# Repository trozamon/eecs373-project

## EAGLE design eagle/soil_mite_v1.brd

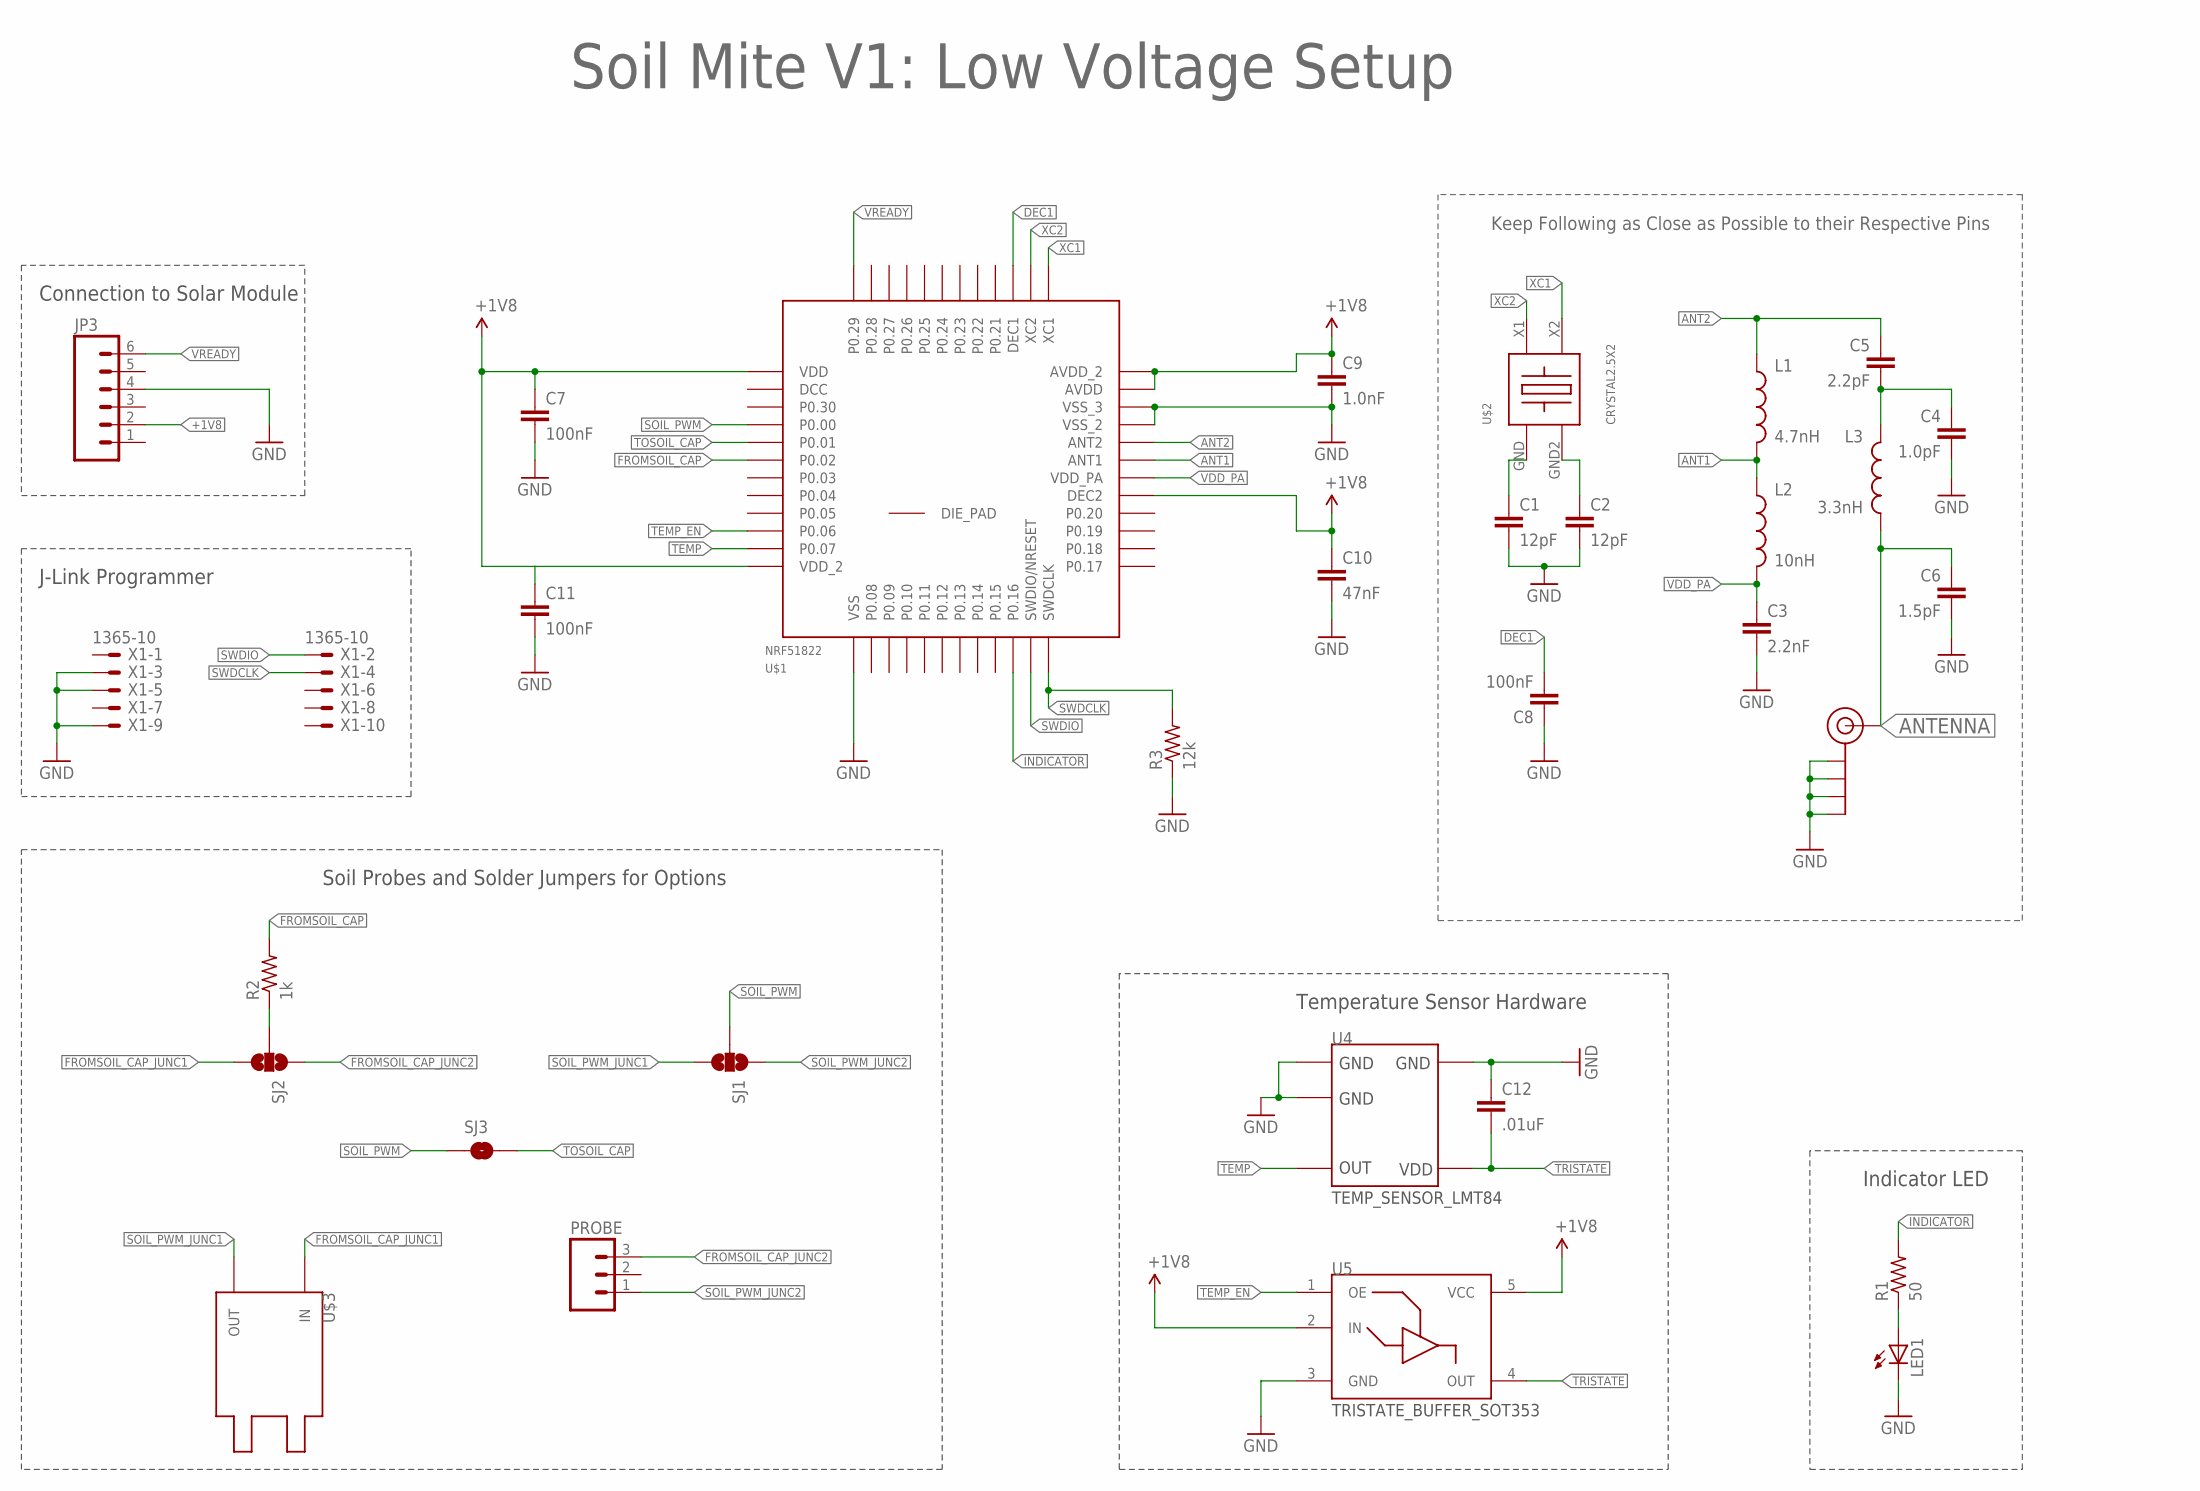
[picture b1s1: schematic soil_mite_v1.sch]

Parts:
C1, C2: 12pF; 0402-CAP
C3: 2.2nF; 0402-CAP
C4: 1.0pF; 0402-CAP
C5: 2.2pF; 0402-CAP
C6: 1.5pF; 0402-CAP
C7, C8, C11: 100nF; 0402-CAP
C9: 1.0nF; 0402-CAP
C10: 47nF; 0402-CAP
C12: .01uF; 0402-CAP
J$1: SMA_EDGE; SMA-EDGE
JP3: M06POLAR; MOLEX-1X6
L1: 4.7nH; C0402
L2: 10nH; C0402
L3: 3.3nH; C0402
LED1: JON_LIB_LEDCHIPLED_0603; JON_LIB_CHIPLED_0603
PROBE: M03PTH; 1X03
R1: 50; R0603
R2: 1k; R0603
R3: 12k; RCL_R0402
SJ1, SJ2: SOLDERJUMPER_2WAYT; SJ_2
SJ3: SOLDERJUMPERNO; SJ_2S-NO
U4: TEMP_SENSOR_LMT84; SOT353
U5: TRISTATE_BUFFER_SOT353; SOT353
U$1: NRF51822; QFN48
U$2: CRYSTAL2.5X2; 2.5X2MM
U$3: SOIL_PROBE_TOP_TOPOUT-IN; PROBE_LAYOUT_1_OUT-IN
X1: 1365-10

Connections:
+1V8: C7.1, C9.1, C10.1, C11.1, JP3.2, U5.2 (IN), U5.5 (VCC), U$1.1 (VDD), U$1.12 (VDD_2), U$1.29 (DEC2), U$1.35 (AVDD), U$1.36 (AVDD_2)
ANT1: L1.2, L2.1, U$1.31 (ANT1)
ANT2: C5.1, L1.1, U$1.32 (ANT2)
ANTENNA: C6.1, J$1.SIG (SIGNAL), L3.2
DEC1: C8.2, U$1.39 (DEC1)
FROMSOIL_CAP: R2.1, R2.2, SJ2.2, U$1.6 (P0.02)
FROMSOIL_CAP_JUNC1: SJ2.3, U$3.IN
FROMSOIL_CAP_JUNC2: PROBE.3, SJ2.1
GND: C1.2, C2.2, C3.2, C4.2, C6.2, C7.2, C8.1, C9.2, C10.2, C11.2, C12.1, J$1.GND@0 (GND), J$1.GND@1 (GND), J$1.GND@2 (GND), J$1.GND@3 (GND), JP3.4, LED1.C, R3.1, U4.1 (GND), U4.2 (GND), U4.5 (GND), U5.3 (GND), U$1.13 (VSS), U$1.33 (VSS_2), U$1.34 (VSS_3), X1.3, X1.5, X1.9
INDICATOR: R1.2, U$1.22 (P0.16)
unnamed: C1.1, U$2.GND
unnamed: C2.1, U$2.GND2
unnamed: LED1.A, R1.1
unnamed: C4.1, C5.2, L3.1
SOIL_PWM: SJ1.2, SJ3.1, U$1.4 (P0.00)
SOIL_PWM_JUNC1: SJ1.3, U$3.OUT
SOIL_PWM_JUNC2: PROBE.1, SJ1.1
SWDCLK: R3.2, U$1.24 (SWDCLK), X1.4
SWDIO: U$1.23 (SWDIO/NRESET), X1.2
TEMP: U4.3 (OUT), U$1.11 (P0.07)
TEMP_EN: U5.1 (OE), U$1.10 (P0.06)
TOSOIL_CAP: SJ3.2, U$1.5 (P0.01)
TRISTATE: C12.2, U4.4 (VDD), U5.4 (OUT)
VDD_PA: C3.1, L2.2, U$1.30 (VDD_PA)
VREADY: JP3.6, U$1.48 (P0.29)
XC1: U$1.37 (XC1), U$2.X2
XC2: U$1.38 (XC2), U$2.X1

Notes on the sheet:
Soil Mite V1: Low Voltage Setup
Keep Following as Close as Possible to their Respective Pins
Connection to Solar Module
J-Link Programmer
Soil Probes and Solder Jumpers for Options
Temperature Sensor Hardware
Indicator LED

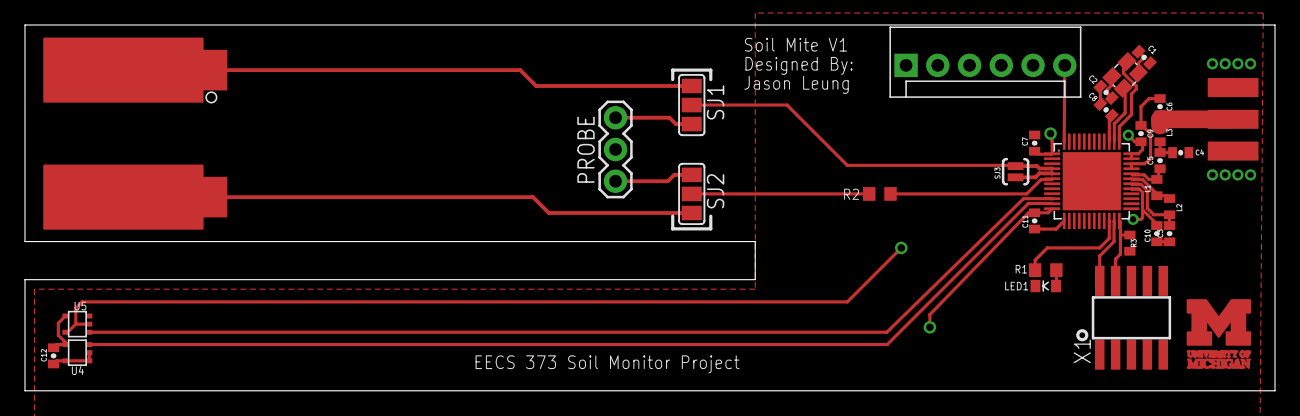
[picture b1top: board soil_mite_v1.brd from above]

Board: 4 copper layers, 100.0 x 29.3 mm, 32 parts (0 on the bottom side), 27 nets.

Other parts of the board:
U$5: BLOCK-M-DOUBLE-STACKED-5MM_MASK

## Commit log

2014-11-02 Add proposal, Makefiles
2014-11-02 Updat Makefile, add pics
2014-11-03 Update diagrams, proposal
2014-11-10 Start system document, it's pretty jank right now.
2014-11-12 Update system document
2014-11-13 Update system documentation
2014-11-16 Add power circuit schematic
2014-11-21 Update power schematic
2014-11-21 Add temp sensor to system docs
2014-11-21 added completed schematic but incomplete board. if you need explanations of parts of the board feel free to ping me
2014-11-21 Finish schematic, assigning footprints
2014-11-21 Finish power component to footprint mapping
2014-11-22 Finalize schematic
2014-11-22 Add initial power board design
2014-11-23 updated files. need to understand new components
2014-11-23 need to route board. 'layout' part done. need eagle professional to finish
2014-11-23 finished layout. let me know if there are glaring errors
2014-11-23 Minor updates to power schematic and board
2014-11-23 Add pull-downs to NMOS gates on power board
2014-11-23 Update gitignore
2014-11-23 finalized soil mite design. sending out for shipping
2014-11-23 Add gerber stuffz
2014-12-03 Redo power schematic
2014-12-03 Finish power schematic bugfixes
2014-12-03 Attach footprints to components
2014-12-03 Small fixes to schematic, netlist
2014-12-03 Layout PCB
2014-12-03 Finish PCB layout
2014-12-03 Update zip generation
2014-12-04 Add nordic chip code.
2014-12-06 add ADC
2014-12-07 Add enclosure v1
2014-12-07 Add initial plotting script, reference power board build files
2014-12-07 Moisture plot is how human-readable
2014-12-07 Start temp sensor, disable prescaling
2014-12-07 Update low bound for time delay in moisture plot
2014-12-08 Add soak data, R script for soak plot
2014-12-08 Update EnclosureBottom

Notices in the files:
parts and their libraries:
SparkFun-Capacitors: Licensing: CC v3.0 Share-Alike You are welcome to use this library for commercial purposes.
